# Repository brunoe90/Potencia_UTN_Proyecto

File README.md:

# Potencia_UTN_Proyecto
Proyecto de Potencia UTN

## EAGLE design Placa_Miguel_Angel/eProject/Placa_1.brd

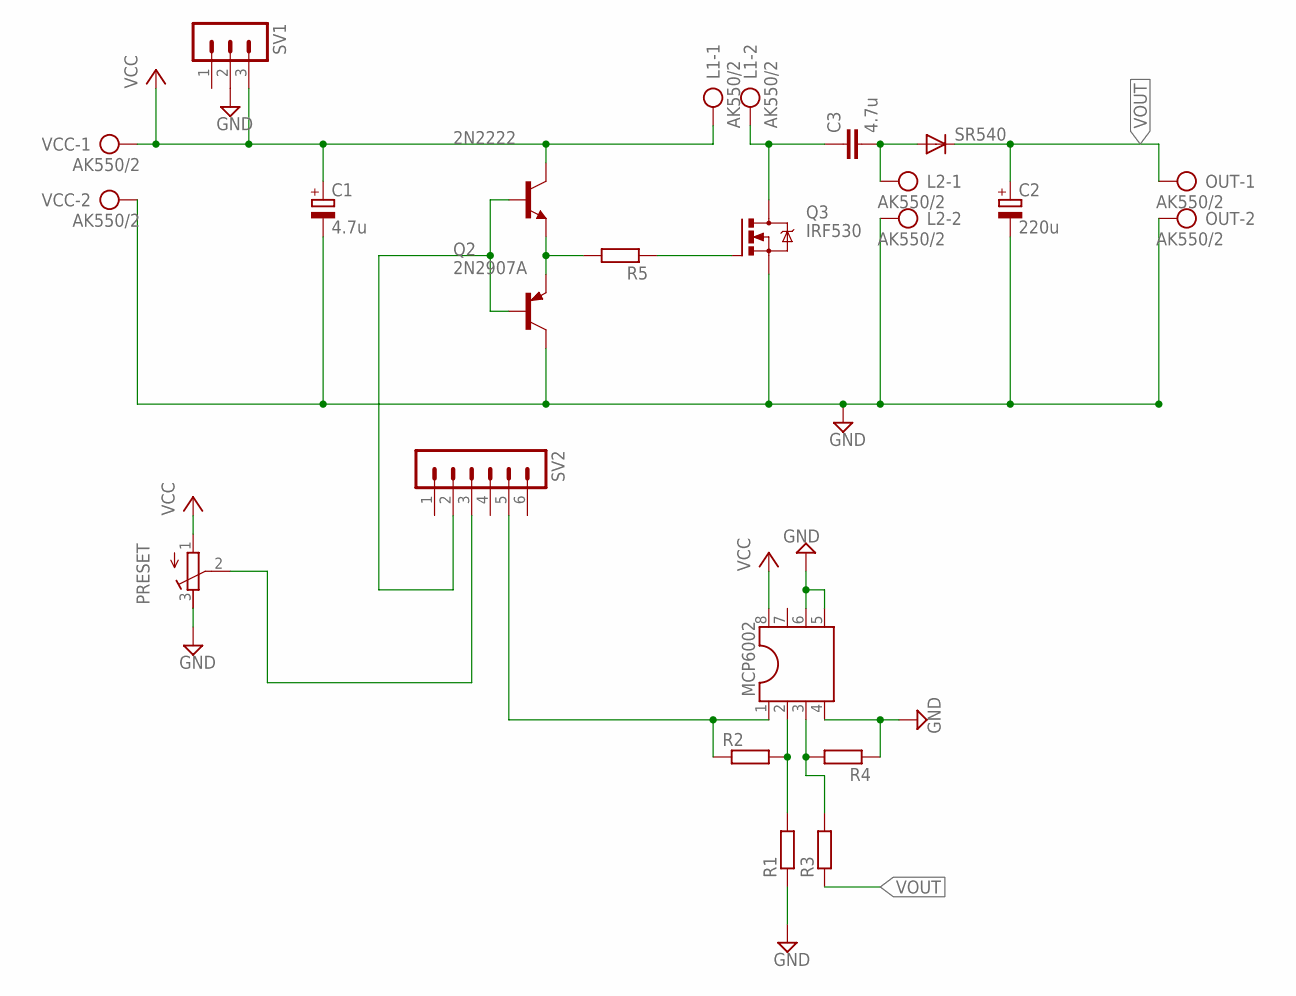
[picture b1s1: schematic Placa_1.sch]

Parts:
2N2222: 2N2222-NPN-TO92-EBC; TO92-EBC
C1: 4.7u; E5-8,5
C2: 220u; E5-8,5
C3: 4.7u; C075-052X106
L1, L2: AK550/2
MCP6002: DIL8; DIL08
OUT: AK550/2
PRESET: R-TRIMM64W; RTRIM64W
Q2: 2N2907A; TO18
Q3: IRF530; TO220BV
R1, R2, R3, R4, R5: R-EU_0207/10; 0207/10
SR540: DIODE-DO27-15; DO27-15
SV1: MA03-1
SV2: MA06-1
VCC: AK550/2

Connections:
GND: C1.-, C2.-, L2.2, MCP6002.4, MCP6002.5, MCP6002.6, OUT.2, PRESET.3 (E), Q2.3 (C), Q3.S, R1.1, R4.1, SV1.2, VCC.2
unnamed: PRESET.2 (S), SV2.3
unnamed: C3.1, L1.2, Q3.D
unnamed: C3.2, L2.1, SR540.A
unnamed: 2N2222.E, Q2.1 (E), R5.2
unnamed: MCP6002.3, R3.2, R4.2
unnamed: 2N2222.B, Q2.2 (B), SV2.2
unnamed: MCP6002.2, R1.2, R2.2
unnamed: MCP6002.1, R2.1, SV2.5
unnamed: Q3.G, R5.1
VCC: 2N2222.C, C1.+, L1.1, MCP6002.8, PRESET.1 (A), SV1.3, VCC.1
VOUT: C2.+, OUT.1, R3.1, SR540.C

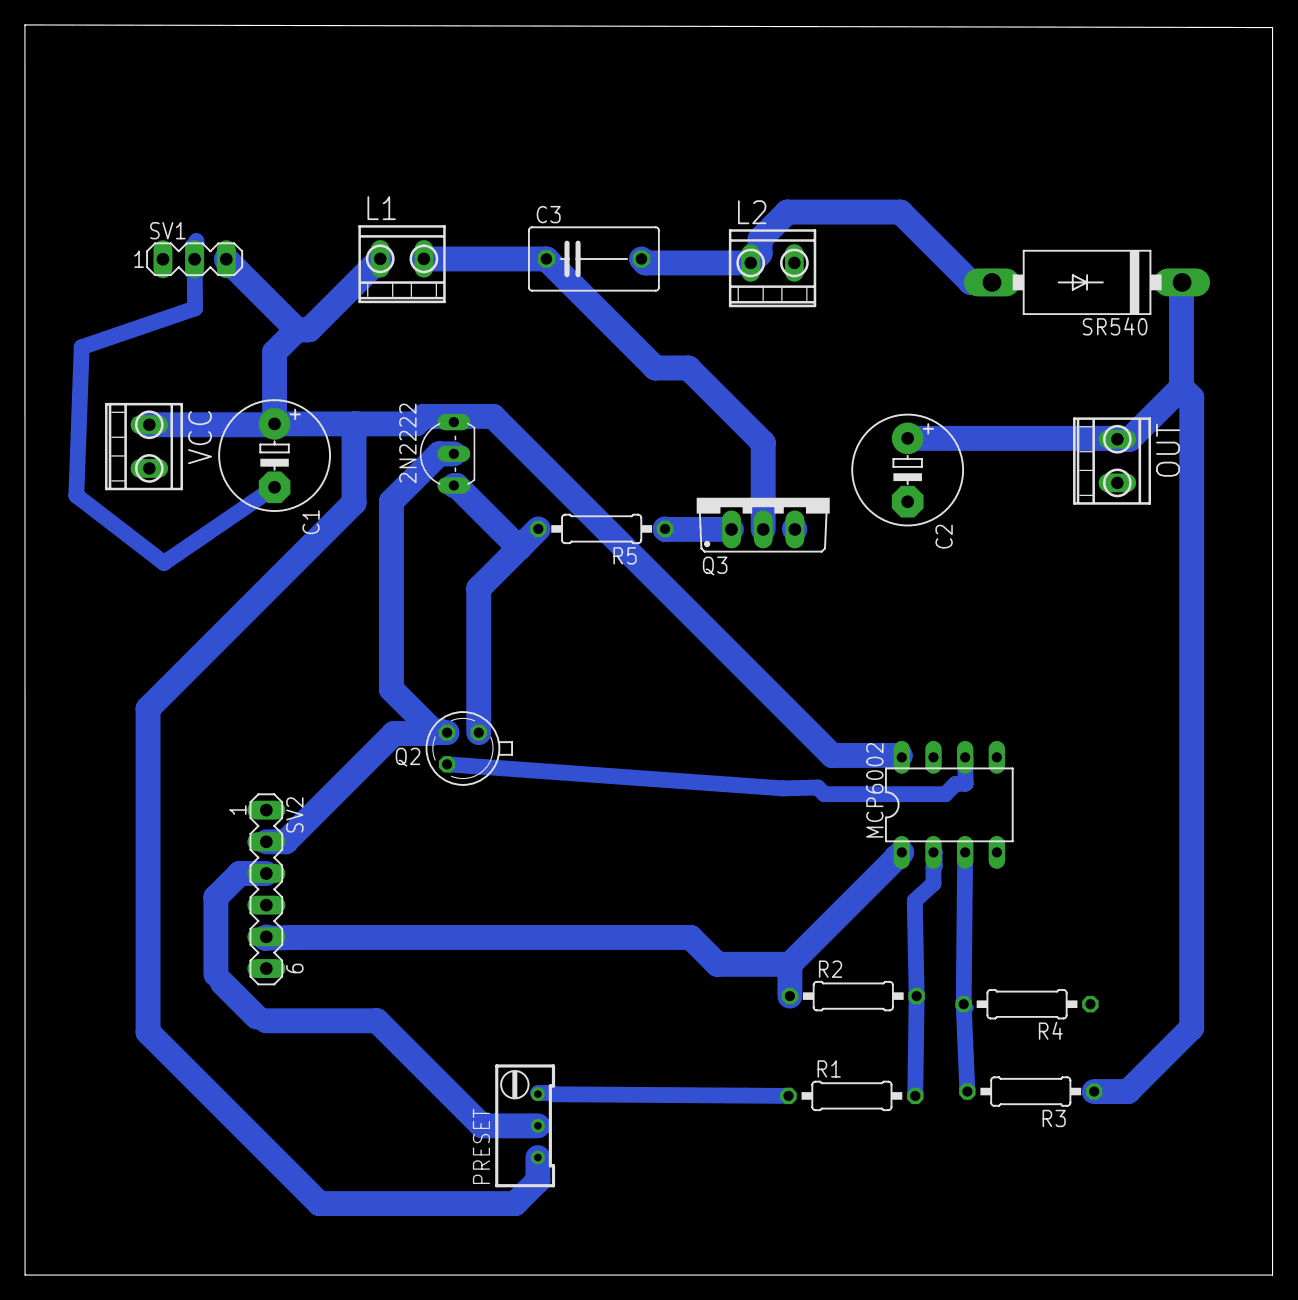
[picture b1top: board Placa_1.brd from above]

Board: 2 copper layers, 100.0 x 100.2 mm, 20 parts (0 on the bottom side), 12 nets.

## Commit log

2017-10-01 Primer Commit todo los garchayectos
2017-10-02 placa
2017-10-07 Se terminó el schematic
2017-10-07 pablo manco
2017-10-09 se termino la placa a soldar
